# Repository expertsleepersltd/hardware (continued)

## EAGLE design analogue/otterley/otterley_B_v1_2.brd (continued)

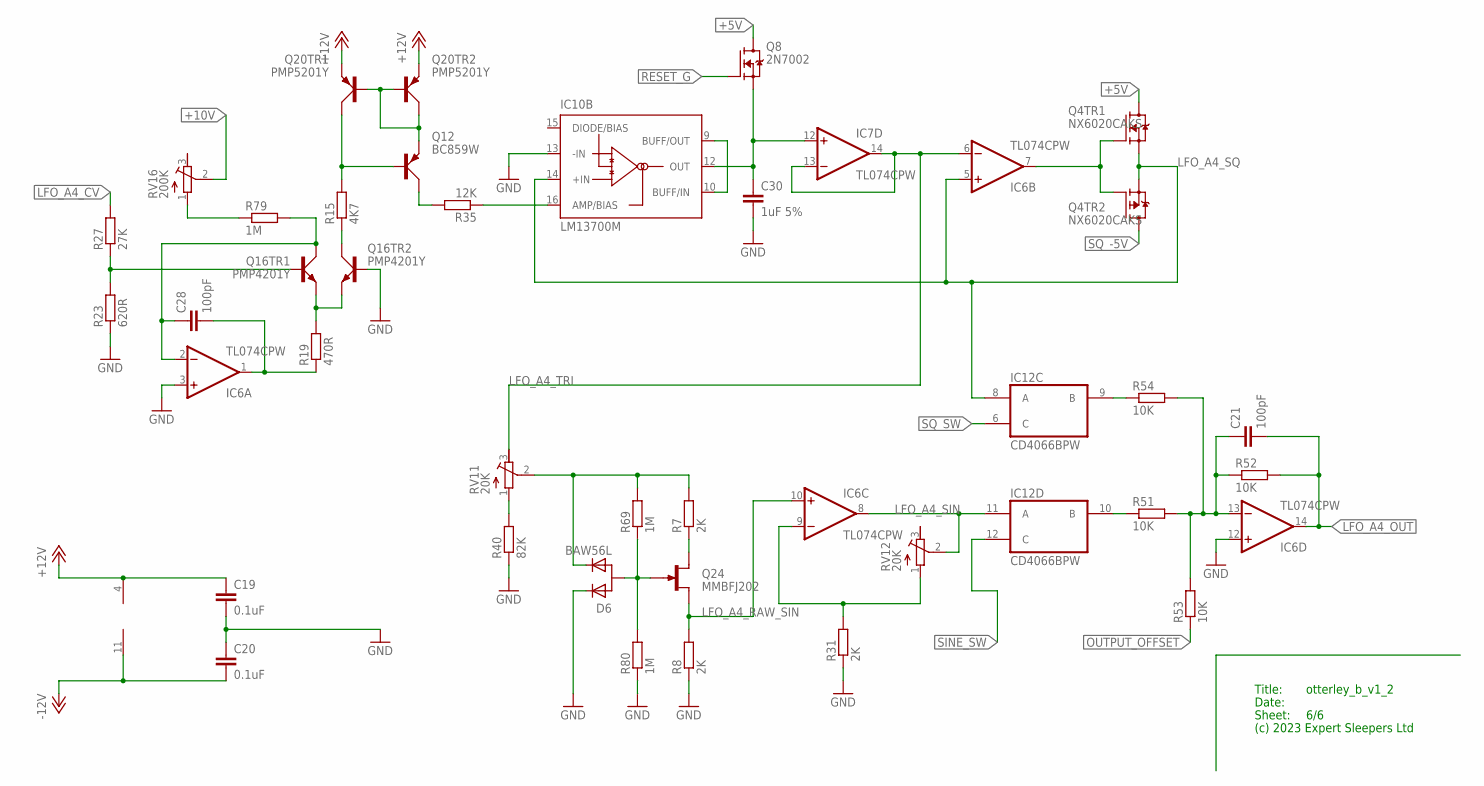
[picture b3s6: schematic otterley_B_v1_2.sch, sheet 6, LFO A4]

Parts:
C19, C20: 0.1uF; C0402
C21, C28: 100pF; C0603
C30: 1uF 5%; C0805
D6: BAW56L; SOT-23
IC6, IC7: TL074CPW; PW_R-PDSO-G14
IC10: LM13700M; SO16
IC12: CD4066BPW; PW_R-PDSO-G14
Q4: NX6020CAKS; SOT363
Q8: 2N7002; SOT23
Q12: BC859W; SOT323
Q16: PMP4201Y; SOT65P210X110-6N
Q20: PMP5201Y; SOT65P210X110-6N
Q24: MMBFJ202; SOT23
R7, R8, R31: 2K; R0603
R15: 4K7; R0603
R19: 470R; R0603
R23: 620R; R0603
R27: 27K; R0603
R35: 12K; R0603
R40: 82K; R0603
R51, R52, R53, R54: 10K; R0603
R69, R79, R80: 1M; R0603
RV11, RV12: 20K; TC33X
RV16: 200K; TC33X

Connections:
+5V: Q4.6 (D), Q8.3 (D); also elsewhere on the board
+10V: RV16.2 (S); also elsewhere on the board
+12V: C19.1, IC6.4 (V+), Q20.4 (E), Q20.5 (E); also elsewhere on the board
-12V: C20.2, IC6.11 (V-); also elsewhere on the board
GND: C19.2, C20.1, C30.2, D6.1 (C1), IC6.3 (+IN), IC6.12 (+IN), IC10.13 (-IN), Q16.2 (B), R8.1, R23.1, R31.1, R40.1, R80.1; also elsewhere on the board
LFO_A4_CV: R27.2; also elsewhere on the board
LFO_A4_OUT: C21.2, IC6.14 (OUT), R52.2; also elsewhere on the board
LFO_A4_RAW_SIN: IC6.10 (+IN), Q24.2 (S), R8.2
LFO_A4_SIN: IC6.8 (OUT), IC12.11 (A), RV12.2 (S)
LFO_A4_SQ: IC6.5 (+IN), IC10.14 (+IN), IC12.8 (A), Q4.1 (S), Q4.4 (S)
LFO_A4_TRI: IC6.6 (-IN), IC7.13 (-IN), IC7.14 (OUT), RV11.3 (E)
unnamed: IC12.9 (B), R54.1
unnamed: IC10.9 (BUFF/OUT), IC10.10 (BUFF/IN)
unnamed: C30.1, IC7.12 (+IN), IC10.12 (OUT), Q8.2 (S)
unnamed: IC10.16 (AMP/BIAS), R35.1
unnamed: C28.1, IC6.2 (-IN), Q16.6 (C), R79.2
unnamed: C28.2, IC6.1 (OUT), R19.1
unnamed: Q16.4 (E), Q16.5 (E), R19.2
unnamed: Q12.3 (C), R35.2
unnamed: Q12.1 (B), Q20.6 (C), R15.2
unnamed: Q12.2 (E), Q20.1 (B), Q20.2 (B), Q20.3 (C)
unnamed: Q16.3 (C), R15.1
unnamed: R40.2, RV11.1 (A)
unnamed: D6.2 (C2), R7.2, R69.2, RV11.2 (S)
unnamed: D6.3 (A), Q24.3 (G), R69.1, R80.2
unnamed: Q24.1 (D), R7.1
unnamed: IC6.9 (-IN), R31.2, RV12.1 (A)
unnamed: C21.1, IC6.13 (-IN), R51.2, R52.1, R53.2, R54.2
unnamed: IC6.7 (OUT), Q4.2 (G), Q4.5 (G)
unnamed: IC12.10 (B), R51.1
unnamed: R79.1, RV16.1 (A)
unnamed: Q16.1 (B), R23.2, R27.1
OUTPUT_OFFSET: R53.1; also elsewhere on the board
RESET_G: Q8.1 (G); also elsewhere on the board
SINE_SW: IC12.12 (C); also elsewhere on the board
SQ_-5V: Q4.3 (D); also elsewhere on the board
SQ_SW: IC12.6 (C); also elsewhere on the board

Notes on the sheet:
Title:
Date:
Sheet:
(c) 2023 Expert Sleepers Ltd

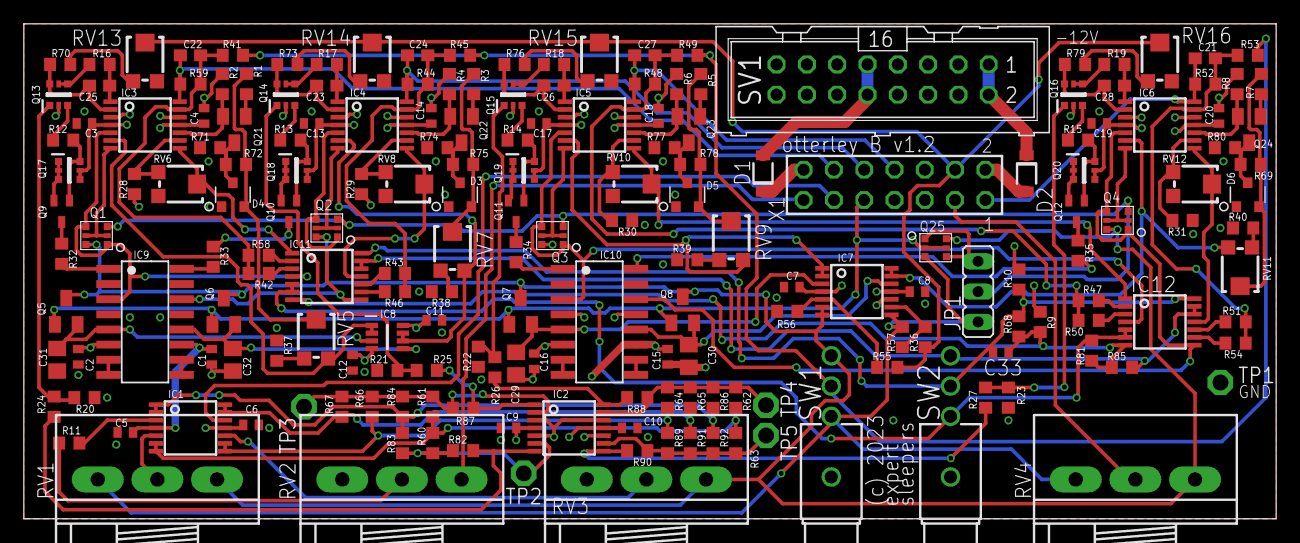
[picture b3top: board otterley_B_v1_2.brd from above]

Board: 4 copper layers, 105.0 x 41.5 mm, 194 parts (0 on the bottom side), 141 nets.

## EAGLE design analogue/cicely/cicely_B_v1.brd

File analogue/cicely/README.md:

Cicely
======

https://expert-sleepers.co.uk/cicely.html

Copyright (c) 2023 Expert Sleepers Ltd

Please refer to [LICENSE.md](LICENSE.md) for licensing information.

Please note that Expert Sleepers® is a registered trade mark in the UK, the European Union, and the United States. Remove any branding before making a derivative work.

Front panel layout is [here](../../panels).

Board and schematic are in [EAGLE](https://en.wikipedia.org/wiki/EAGLE_(program)) format.

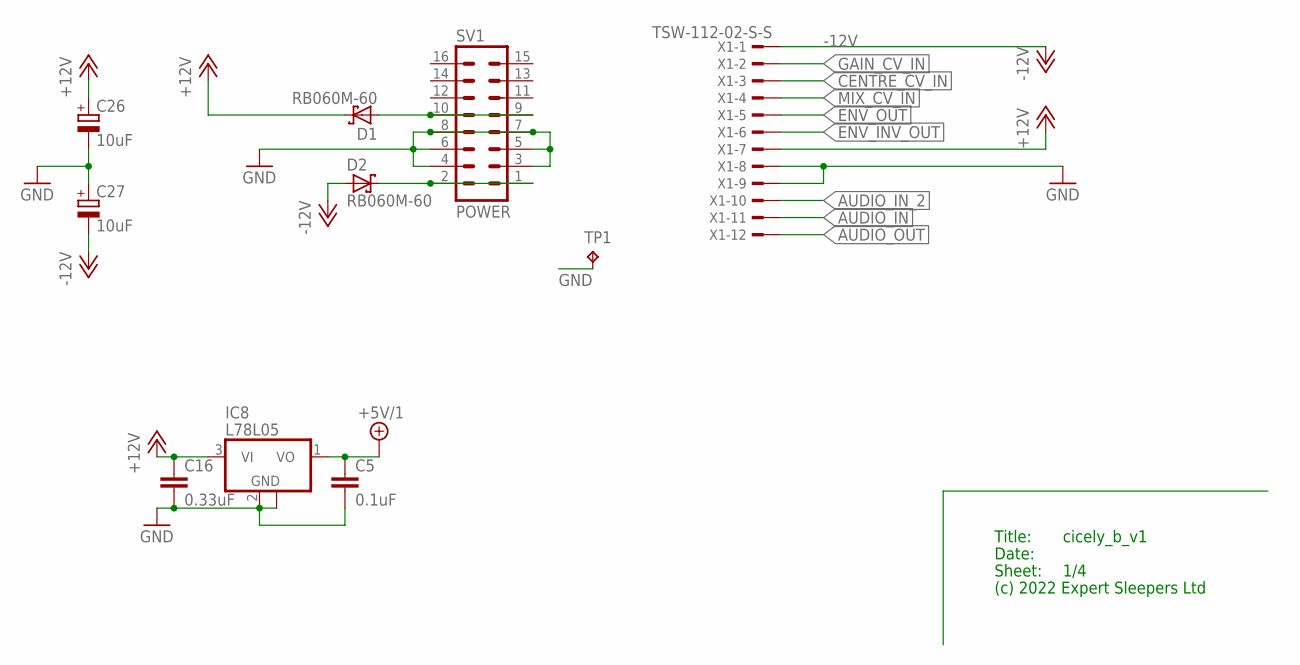
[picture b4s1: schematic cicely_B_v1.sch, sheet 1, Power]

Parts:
C5: 0.1uF; C0402
C16: 0.33uF; C0805
C26, C27: 10uF; UD-4X5,8_NICHICON
D1, D2: RB060M-60; SOD123FL
IC8: L78L05; SOT89
SV1: POWER; ML16
TP1: RA2; P1-13
X1: TSW-112-02-S-S

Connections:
+5V/1: C5.1, IC8.1 (VO); also elsewhere on the board
+12V: C16.1, C26.+, D1.C, IC8.3 (VI), X1.7; also elsewhere on the board
-12V: C27.-, D2.A, X1.1; also elsewhere on the board
AUDIO_IN: X1.11; also elsewhere on the board
AUDIO_IN_2: X1.10; also elsewhere on the board
AUDIO_OUT: X1.12; also elsewhere on the board
CENTRE_CV_IN: X1.3; also elsewhere on the board
ENV_INV_OUT: X1.6; also elsewhere on the board
ENV_OUT: X1.5; also elsewhere on the board
GAIN_CV_IN: X1.2; also elsewhere on the board
GND: C5.2, C16.2, C26.-, C27.+, IC8.2 (GND), IC8.2@1 (GND), SV1.3, SV1.4, SV1.5, SV1.6, SV1.7, SV1.8, TP1.TP, X1.8, X1.9; also elsewhere on the board
MIX_CV_IN: X1.4; also elsewhere on the board
unnamed: D2.C, SV1.1, SV1.2
unnamed: D1.A, SV1.9, SV1.10

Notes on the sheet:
Title:
Date:
Sheet:
(c) 2022 Expert Sleepers Ltd

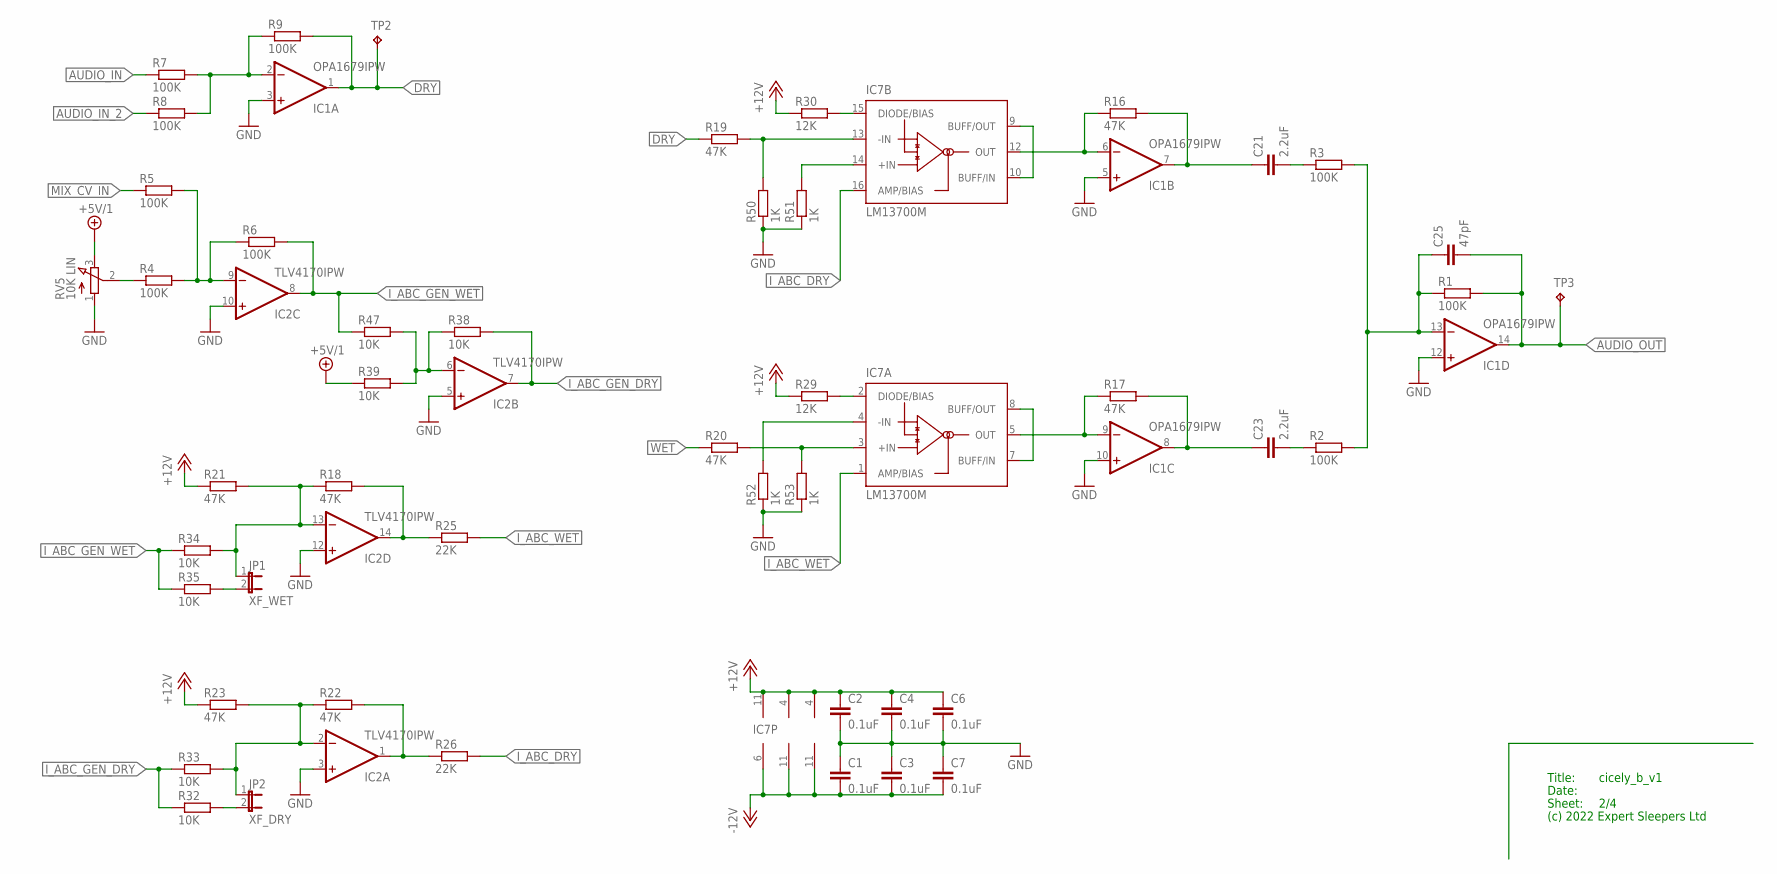
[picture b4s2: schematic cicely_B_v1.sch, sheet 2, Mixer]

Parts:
C1, C2, C3, C4, C6, C7: 0.1uF; C0402
C21, C23: 2.2uF; C0805
C25: 47pF; C0603
IC1: OPA1679IPW; PW_R-PDSO-G14
IC2: TLV4170IPW; PW_R-PDSO-G14
IC7: LM13700M; SO16
JP1: XF_WET; JP1
JP2: XF_DRY; JP1
R1, R2, R3, R4, R5, R6, R7, R8, R9: 100K; R0603
R16, R17, R18, R19, R20, R21, R22, R23: 47K; R0603
R25, R26: 22K; R0603
R29, R30: 12K; R0603
R32, R33, R34, R35, R38, R39, R47: 10K; R0603
R50, R51, R52, R53: 1K; R0603
RV5: 10K LIN; RD1610NOA0X
TP2, TP3: RA2; P1-13

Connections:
+5V/1: R39.1, RV5.3 (E); also elsewhere on the board
+12V: C2.1, C4.1, C6.1, IC1.4 (V+), IC2.4 (V+), IC7.11 (V+), R21.1, R23.1, R29.1, R30.1; also elsewhere on the board
-12V: C1.2, C3.2, C7.2, IC1.11 (V-), IC2.11 (V-), IC7.6 (V-); also elsewhere on the board
AUDIO_IN: R7.1; also elsewhere on the board
AUDIO_IN_2: R8.1; also elsewhere on the board
AUDIO_OUT: C25.2, IC1.14 (OUT), R1.2, TP3.TP; also elsewhere on the board
DRY: IC1.1 (OUT), R9.2, R19.1, TP2.TP; also elsewhere on the board
GND: C1.1, C2.2, C3.1, C4.2, C6.2, C7.1, IC1.3 (+IN), IC1.5 (+IN), IC1.10 (+IN), IC1.12 (+IN), IC2.3 (+IN), IC2.5 (+IN), IC2.10 (+IN), IC2.12 (+IN), R50.1, R51.1, R52.1, R53.1, RV5.1 (A); also elsewhere on the board
I_ABC_DRY: IC7.16 (AMP/BIAS), R26.2
I_ABC_GEN_DRY: IC2.7 (OUT), R32.1, R33.1, R38.2
I_ABC_GEN_WET: IC2.8 (OUT), R6.2, R34.1, R35.1, R47.1
I_ABC_WET: IC7.1 (AMP/BIAS), R25.2
MIX_CV_IN: R5.1; also elsewhere on the board
unnamed: C25.1, IC1.13 (-IN), R1.1, R2.2, R3.2
unnamed: R4.1, RV5.2 (S)
unnamed: IC7.15 (DIODE/BIAS), R30.2
unnamed: IC1.9 (-IN), IC7.5 (OUT), R17.1
unnamed: IC7.2 (DIODE/BIAS), R29.2
unnamed: IC1.6 (-IN), IC7.12 (OUT), R16.1
unnamed: C23.1, IC1.8 (OUT), R17.2
unnamed: IC2.9 (-IN), R4.2, R5.2, R6.1
unnamed: C21.1, IC1.7 (OUT), R16.2
unnamed: IC7.3 (+IN), R20.2, R53.2
unnamed: IC7.4 (-IN), R52.2
unnamed: IC2.13 (-IN), JP1.1, R18.1, R21.2, R34.2
unnamed: IC2.6 (-IN), R38.1, R39.2, R47.2
unnamed: IC2.14 (OUT), R18.2, R25.1
unnamed: IC2.1 (OUT), R22.2, R26.1
unnamed: IC2.2 (-IN), JP2.1, R22.1, R23.2, R33.2
unnamed: IC7.14 (+IN), R51.2
unnamed: IC7.13 (-IN), R19.2, R50.2
unnamed: C21.2, R3.1
unnamed: C23.2, R2.1
unnamed: IC7.9 (BUFF/OUT), IC7.10 (BUFF/IN)
unnamed: IC7.7 (BUFF/IN), IC7.8 (BUFF/OUT)
unnamed: IC1.2 (-IN), R7.2, R8.2, R9.1
unnamed: JP2.2, R32.2
unnamed: JP1.2, R35.2
WET: R20.1; also elsewhere on the board

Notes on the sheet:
Title:
Date:
Sheet:
(c) 2022 Expert Sleepers Ltd

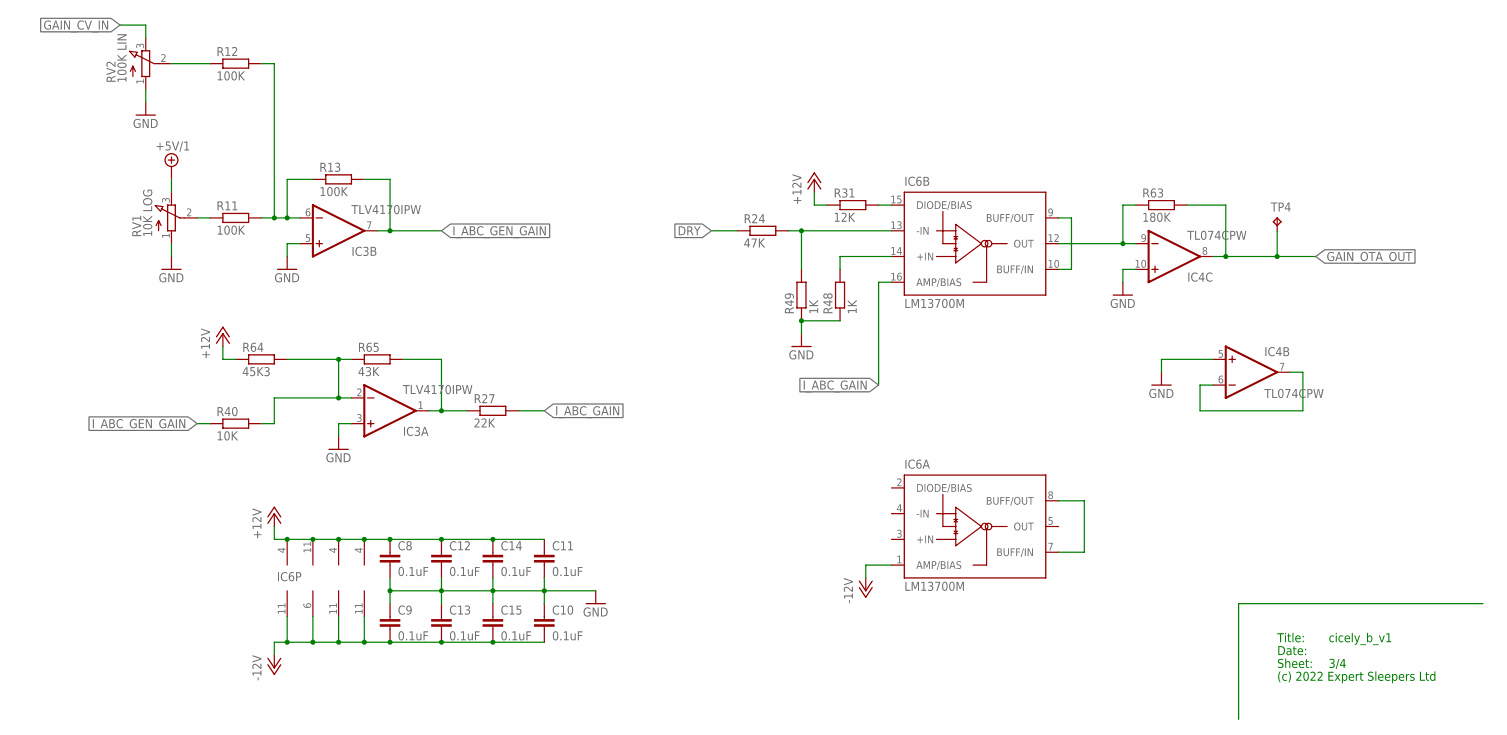
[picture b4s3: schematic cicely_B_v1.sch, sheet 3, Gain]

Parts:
C8, C9, C10, C11, C12, C13, C14, C15: 0.1uF; C0402
IC3: TLV4170IPW; PW_R-PDSO-G14
IC4, IC5: TL074CPW; PW_R-PDSO-G14
IC6: LM13700M; SO16
R11, R12, R13: 100K; R0603
R24: 47K; R0603
R27: 22K; R0603
R31: 12K; R0603
R40: 10K; R0603
R48, R49: 1K; R0603
R63: 180K; R0603
R64: 45K3; R0603
R65: 43K; R0603
RV1: 10K LOG; RD1610NOA0X
RV2: 100K LIN; RD1610NOA0X
TP4: RA2; P1-13

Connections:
+5V/1: RV1.3 (E); also elsewhere on the board
+12V: C8.1, C11.1, C12.1, C14.1, IC3.4 (V+), IC4.4 (V+), IC5.4 (V+), IC6.11 (V+), R31.1, R64.1; also elsewhere on the board
-12V: C9.2, C10.2, C13.2, C15.2, IC3.11 (V-), IC4.11 (V-), IC5.11 (V-), IC6.1 (AMP/BIAS), IC6.6 (V-); also elsewhere on the board
DRY: R24.1; also elsewhere on the board
GAIN_CV_IN: RV2.3 (E); also elsewhere on the board
GAIN_OTA_OUT: IC4.8 (OUT), R63.2, TP4.TP; also elsewhere on the board
GND: C8.2, C9.1, C10.1, C11.2, C12.2, C13.1, C14.2, C15.1, IC3.3 (+IN), IC3.5 (+IN), IC4.5 (+IN), IC4.10 (+IN), R48.1, R49.1, RV1.1 (A), RV2.1 (A); also elsewhere on the board
I_ABC_GAIN: IC6.16 (AMP/BIAS), R27.2
I_ABC_GEN_GAIN: IC3.7 (OUT), R13.2, R40.1
unnamed: IC6.9 (BUFF/OUT), IC6.10 (BUFF/IN)
unnamed: IC6.7 (BUFF/IN), IC6.8 (BUFF/OUT)
unnamed: IC6.15 (DIODE/BIAS), R31.2
unnamed: IC4.9 (-IN), IC6.12 (OUT), R63.1
unnamed: IC4.6 (-IN), IC4.7 (OUT)
unnamed: IC6.14 (+IN), R48.2
unnamed: IC6.13 (-IN), R24.2, R49.2
unnamed: R11.1, RV1.2 (S)
unnamed: IC3.6 (-IN), R11.2, R12.2, R13.1
unnamed: IC3.2 (-IN), R40.2, R64.2, R65.1
unnamed: IC3.1 (OUT), R27.1, R65.2
unnamed: R12.1, RV2.2 (S)

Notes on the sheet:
Title:
Date:
Sheet:
(c) 2022 Expert Sleepers Ltd

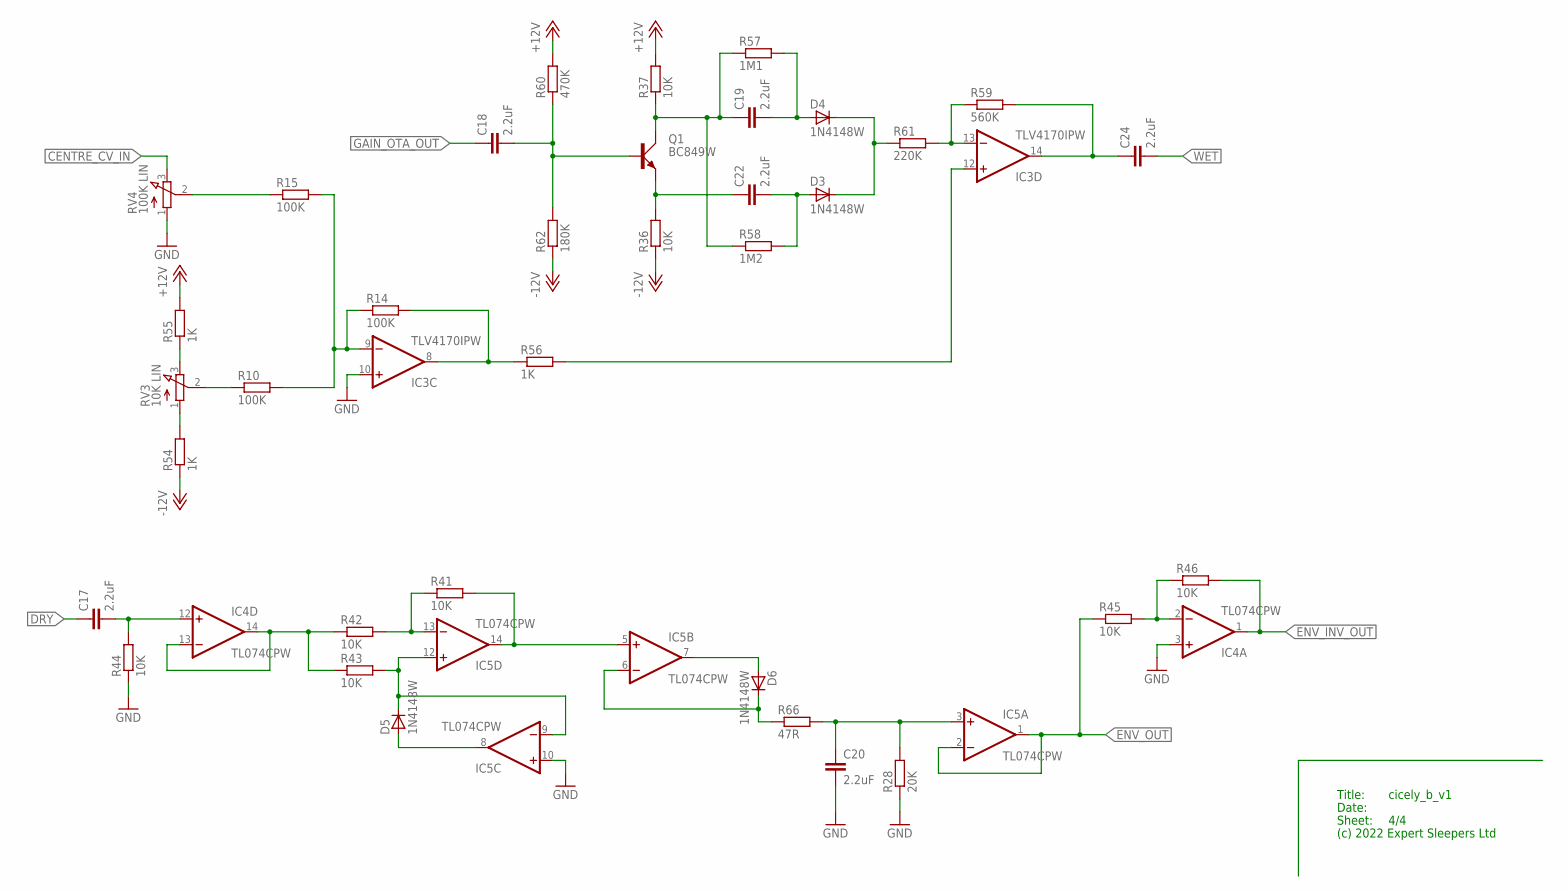
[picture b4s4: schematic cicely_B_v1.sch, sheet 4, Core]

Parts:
C17, C18, C19, C20, C22, C24: 2.2uF; C0805
D3, D4, D5, D6: 1N4148W; SOD123
IC3: TLV4170IPW; PW_R-PDSO-G14
IC4, IC5: TL074CPW; PW_R-PDSO-G14
Q1: BC849W; SOT323
R10, R14, R15: 100K; R0603
R28: 20K; R0603
R36, R37, R41, R42, R43, R44, R45, R46: 10K; R0603
R54, R55, R56: 1K; R0603
R57: 1M1; R0603
R58: 1M2; R0603
R59: 560K; R0603
R60: 470K; R0603
R61: 220K; R0603
R62: 180K; R0603
R66: 47R; R0603
RV3: 10K LIN; RD1610NOA0X
RV4: 100K LIN; RD1610NOA0X

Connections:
+12V: R37.2, R55.2, R60.2; also elsewhere on the board
-12V: R36.1, R54.1, R62.1; also elsewhere on the board
CENTRE_CV_IN: RV4.3 (E); also elsewhere on the board
DRY: C17.1; also elsewhere on the board
DRY_AC: IC4.13 (-IN), IC4.14 (OUT), R42.1, R43.1
ENV_INV_OUT: IC4.1 (OUT), R46.2; also elsewhere on the board
ENV_OUT: IC5.1 (OUT), IC5.2 (-IN), R45.1; also elsewhere on the board
GAIN_OTA_OUT: C18.1; also elsewhere on the board
GND: C20.2, IC3.10 (+IN), IC4.3 (+IN), IC5.10 (+IN), R28.1, R44.1, RV4.1 (A); also elsewhere on the board
unnamed: C17.2, IC4.12 (+IN), R44.2
unnamed: R54.2, RV3.1 (A)
unnamed: R55.1, RV3.3 (E)
unnamed: IC3.12 (+IN), R56.2
unnamed: IC3.13 (-IN), R59.1, R61.2
unnamed: C24.1, IC3.14 (OUT), R59.2
unnamed: R10.1, RV3.2 (S)
unnamed: IC3.9 (-IN), R10.2, R14.1, R15.2
unnamed: C18.2, Q1.1 (B), R60.1, R62.2
unnamed: C19.2, D4.A, R57.2
unnamed: C22.2, D3.A, R58.2
unnamed: C19.1, Q1.3 (C), R37.1, R57.1, R58.1
unnamed: C22.1, Q1.2 (E), R36.2
unnamed: D3.C, D4.C, R61.1
unnamed: IC5.13 (-IN), R41.1, R42.2
unnamed: D6.C, IC5.6 (-IN), R66.1
unnamed: IC5.5 (+IN), IC5.14 (OUT), R41.2
unnamed: D5.C, IC5.9 (-IN), IC5.12 (+IN), R43.2
unnamed: D5.A, IC5.8 (OUT)
unnamed: C20.1, IC5.3 (+IN), R28.2, R66.2
unnamed: D6.A, IC5.7 (OUT)
unnamed: IC4.2 (-IN), R45.2, R46.1
unnamed: R15.1, RV4.2 (S)
VAC_B_CV: IC3.8 (OUT), R14.2, R56.1
WET: C24.2; also elsewhere on the board

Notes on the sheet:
Title:
Date:
Sheet:
(c) 2022 Expert Sleepers Ltd

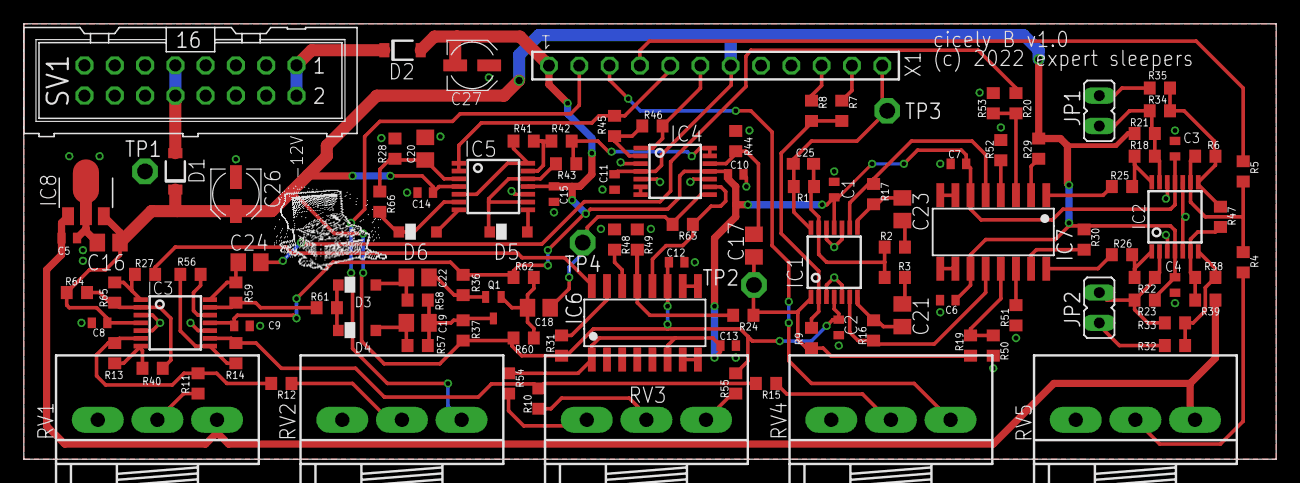
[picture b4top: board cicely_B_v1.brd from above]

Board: 2 copper layers, 105.0 x 36.5 mm, 122 parts (0 on the bottom side), 85 nets.

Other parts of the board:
U$2: TREASURE_10MM_300DPI

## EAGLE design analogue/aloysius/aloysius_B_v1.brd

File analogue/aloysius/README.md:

Aloysius
========

https://expert-sleepers.co.uk/aloysius.html

Copyright (c) 2023 Expert Sleepers Ltd

Please refer to [LICENSE.md](LICENSE.md) for licensing information.

Please note that Expert Sleepers® is a registered trade mark in the UK, the European Union, and the United States. Remove any branding before making a derivative work.

Front panel layout is [here](../../panels).

Board and schematic are in [EAGLE](https://en.wikipedia.org/wiki/EAGLE_(program)) format.

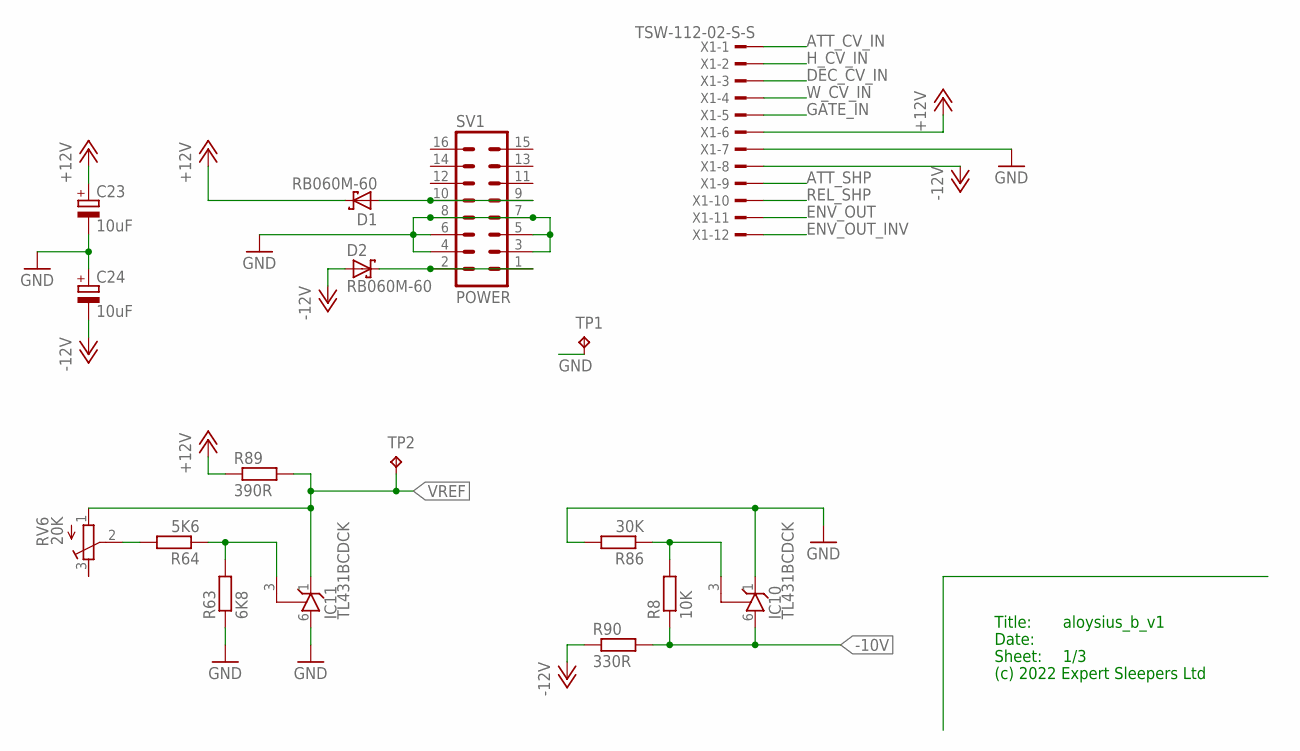
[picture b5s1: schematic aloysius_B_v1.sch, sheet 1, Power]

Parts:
C23, C24: 10uF; UD-4X5,8_NICHICON
D1, D2: RB060M-60; SOD123FL
IC10, IC11: TL431BCDCK; DCK_SC-70
R8: 10K; R0603
R63: 6K8; R0603
R64: 5K6; R0603
R86: 30K; R0603
R89: 390R; R1206
R90: 330R; R1206
RV6: 20K; TC33X
SV1: POWER; ML16
TP1, TP2: RA2; P1-13
X1: TSW-112-02-S-S

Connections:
+12V: C23.+, D1.C, R89.1, X1.6; also elsewhere on the board
-10V: IC10.6 (A), R8.1, R90.2; also elsewhere on the board
-12V: C24.-, D2.A, R90.1, X1.8; also elsewhere on the board
ATT_CV_IN: X1.1; also elsewhere on the board
ATT_SHP: X1.9; also elsewhere on the board
DEC_CV_IN: X1.3; also elsewhere on the board
ENV_OUT: X1.11; also elsewhere on the board
ENV_OUT_INV: X1.12; also elsewhere on the board
GATE_IN: X1.5; also elsewhere on the board
GND: C23.-, C24.+, IC10.1 (C), IC11.6 (A), R63.1, R86.2, SV1.3, SV1.4, SV1.5, SV1.6, SV1.7, SV1.8, TP1.TP, X1.7; also elsewhere on the board
H_CV_IN: X1.2; also elsewhere on the board
unnamed: D2.C, SV1.1, SV1.2
unnamed: D1.A, SV1.9, SV1.10
unnamed: IC11.3 (R), R63.2, R64.1
unnamed: R64.2, RV6.2 (S)
unnamed: IC10.3 (R), R8.2, R86.1
REL_SHP: X1.10; also elsewhere on the board
VREF: IC11.1 (C), R89.2, RV6.1 (A), TP2.TP; also elsewhere on the board
W_CV_IN: X1.4; also elsewhere on the board

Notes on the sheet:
Title:
Date:
Sheet:
(c) 2022 Expert Sleepers Ltd

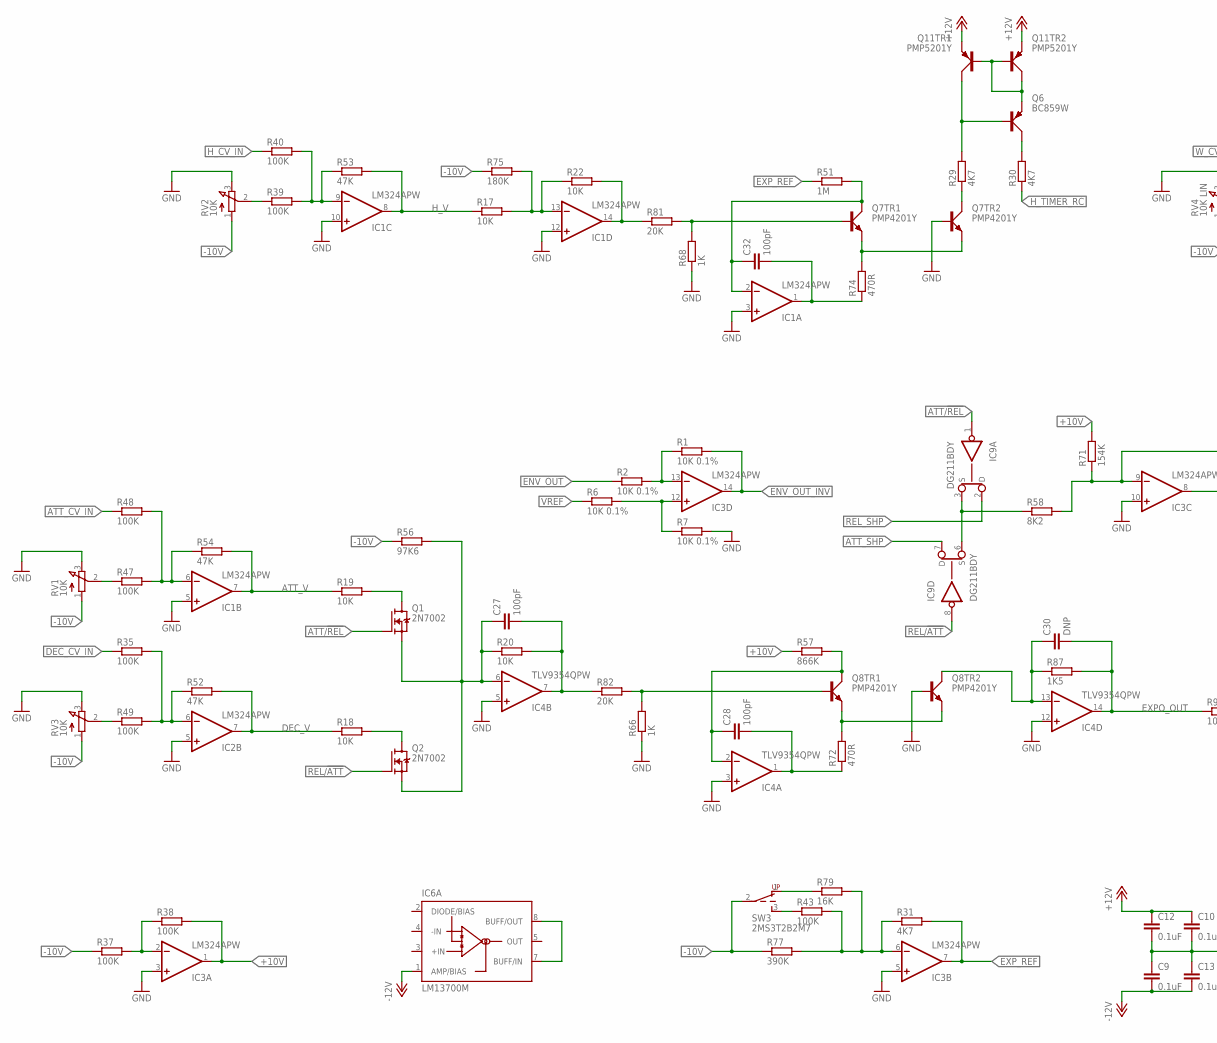
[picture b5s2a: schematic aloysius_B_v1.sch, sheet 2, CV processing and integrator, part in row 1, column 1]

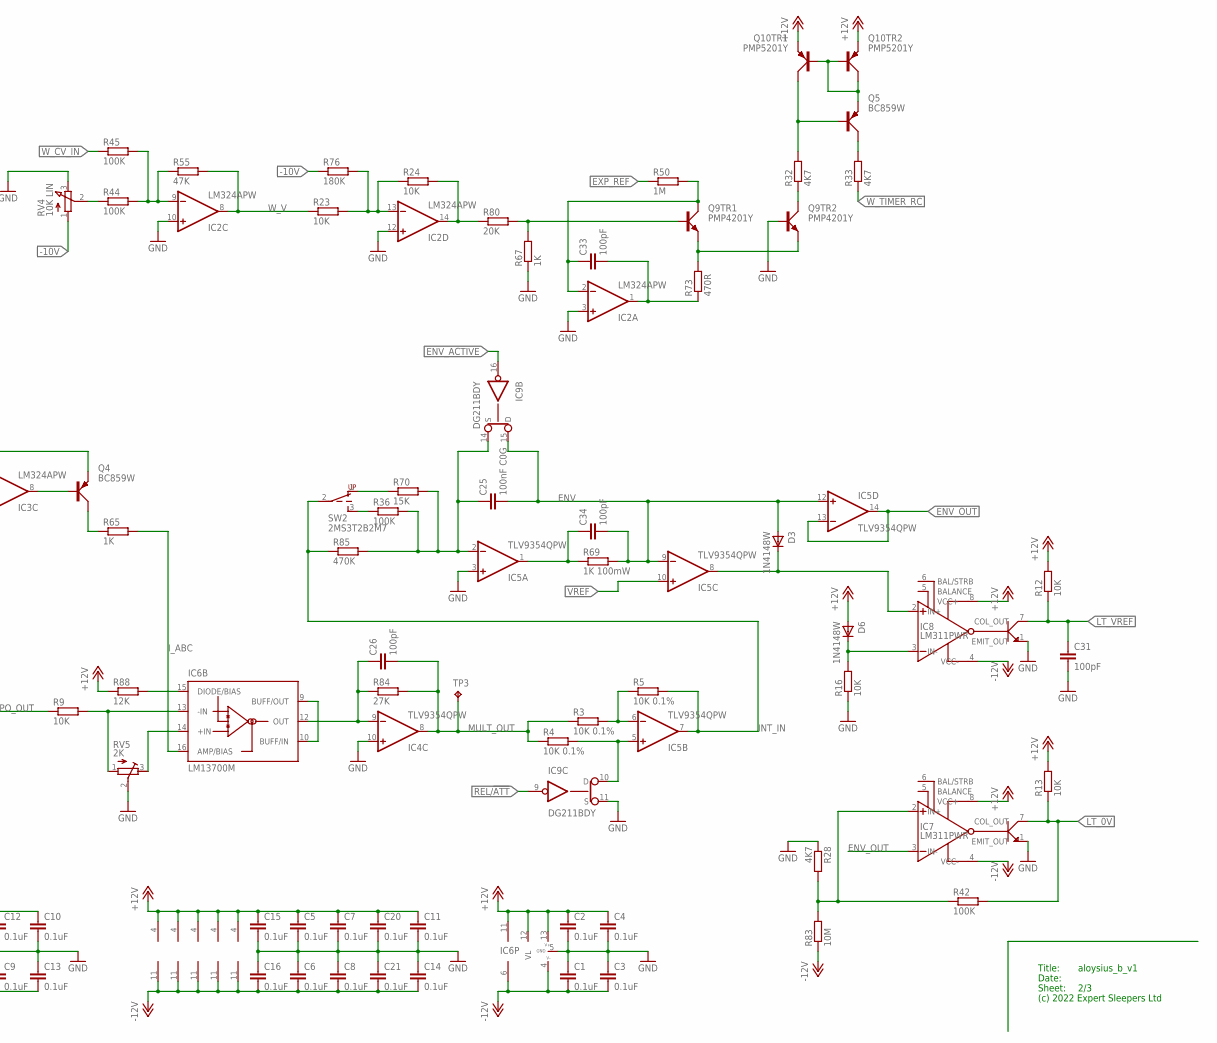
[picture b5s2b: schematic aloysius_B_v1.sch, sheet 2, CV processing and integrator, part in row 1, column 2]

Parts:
C1, C2, C3, C4, C5, C6, C7, C8, C9, C10, C11, C12, C13, C14, C15, C16, C20, C21: 0.1uF; C0402
C25: 100nF C0G; C1206
C26, C27, C28, C31, C32, C33, C34: 100pF; C0603
C30: DNP; C0603
D3, D6: 1N4148W; SOD123
IC1, IC2, IC3: LM324APW; PW_R-PDSO-G14
IC4, IC5: TLV9354QPW; PW_R-PDSO-G14
IC6: LM13700M; SO16
IC7, IC8: LM311PWR; SOP65P640X120-8N
IC9: DG211BDY; SO16
Q1, Q2: 2N7002; SOT23
Q4, Q5, Q6: BC859W; SOT323
Q7, Q8, Q9: PMP4201Y; SOT65P210X110-6N
Q10, Q11: PMP5201Y; SOT65P210X110-6N
R1, R2, R3, R4, R5, R6, R7: 10K 0.1%; R0603
R9, R12, R13, R16, R17, R18, R19, R20, R22, R23, R24: 10K; R0603
R28, R29, R30, R31, R32, R33: 4K7; R0603
R35, R36, R37, R38, R39, R40, R42, R43, R44, R45, R47, R48, R49: 100K; R0603
R50, R51: 1M; R0603
R52, R53, R54, R55: 47K; R0603
R56: 97K6; R0603
R57: 866K; R0603
R58: 8K2; R0603
R65, R66, R67, R68: 1K; R0603
R69: 1K 100mW; R0603
R70: 15K; R0603
R71: 154K; R0603
R72, R73, R74: 470R; R0603
R75, R76: 180K; R0603
R77: 390K; R0603
R79: 16K; R0603
R80, R81, R82: 20K; R0603
R83: 10M; R0603
R84: 27K; R0603
R85: 470K; R0603
R87: 1K5; R0603
R88: 12K; R0603
RV1, RV2, RV3: 10K; RD1610NOA0X
RV4: 10K LIN; RD1610NOA0X
RV5: 2K; RTRIM3296W
SW2, SW3: 2MS3T2B2M7; 2MS1T2B2M7RE
TP3: RA2; P1-13

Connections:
+10V: IC3.1 (OUT), R38.2, R57.1, R71.2
+12V: C2.1, C4.1, C5.1, C7.1, C10.1, C11.1, C12.1, C15.1, C20.1, D6.A, IC1.4 (V+), IC2.4 (V+), IC3.4 (V+), IC4.4 (V+), IC5.4 (V+), IC6.11 (V+), IC7.8 (VCC+), IC8.8 (VCC+), IC9.12 (VL), IC9.13 (V+), Q10.4 (E), Q10.5 (E), Q11.4 (E), Q11.5 (E), R12.2, R13.2, R88.1; also elsewhere on the board
-10V: R37.1, R56.1, R75.1, R76.1, R77.1, RV1.1 (A), RV2.1 (A), RV3.1 (A), RV4.1 (A), SW3.2 (PR); also elsewhere on the board
-12V: C1.2, C3.2, C6.2, C8.2, C9.2, C13.2, C14.2, C16.2, C21.2, IC1.11 (V-), IC2.11 (V-), IC3.11 (V-), IC4.11 (V-), IC5.11 (V-), IC6.1 (AMP/BIAS), IC6.6 (V-), IC7.4 (VCC-), IC8.4 (VCC-), IC9.4 (V-), R83.1; also elsewhere on the board
ATT/!REL: IC9.1 (IN), Q1.1 (G); also elsewhere on the board
ATT_CV_IN: R48.1; also elsewhere on the board
ATT_SHP: IC9.7 (D); also elsewhere on the board
ATT_V: IC1.7 (OUT), R19.1, R54.2
DEC_CV_IN: R35.1; also elsewhere on the board
DEC_V: IC2.7 (OUT), R18.1, R52.2
ENV: C25.2, C34.2, D3.A, IC5.9 (-IN), IC5.12 (+IN), IC9.15 (D), R69.2
ENV_ACTIVE: IC9.16 (IN); also elsewhere on the board
ENV_OUT: IC5.13 (-IN), IC5.14 (OUT), IC7.3 (IN-), R2.1; also elsewhere on the board
ENV_OUT_INV: IC3.14 (OUT), R1.2; also elsewhere on the board
EXPO_OUT: C30.2, IC4.14 (OUT), R9.1, R87.2
EXP_REF: IC3.7 (OUT), R31.2, R50.1, R51.1
GND: C1.1, C2.2, C3.1, C4.2, C5.2, C6.1, C7.2, C8.1, C9.1, C10.2, C11.2, C12.2, C13.1, C14.1, C15.2, C16.1, C20.2, C21.1, C31.2, IC1.3 (+IN), IC1.5 (+IN), IC1.10 (+IN), IC1.12 (+IN), IC2.3 (+IN), IC2.5 (+IN), IC2.10 (+IN), IC2.12 (+IN), IC3.3 (+IN), IC3.5 (+IN), IC3.10 (+IN), IC4.3 (+IN), IC4.5 (+IN), IC4.10 (+IN), IC4.12 (+IN), IC5.3 (+IN), IC7.1 (EMIT_OUT), IC8.1 (EMIT_OUT), IC9.5 (GND), IC9.11 (S), Q7.2 (B), Q8.2 (B), Q9.2 (B), R7.2, R16.1, R28.1, R66.1, R67.1, R68.1, RV1.3 (E), RV2.3 (E), RV3.3 (E), RV4.3 (E), RV5.2 (S); also elsewhere on the board
H_CV_IN: R40.1; also elsewhere on the board
H_TIMER_RC: R30.1; also elsewhere on the board
H_V: IC1.8 (OUT), R17.1, R53.2
INT_IN: IC5.7 (OUT), R5.2, R85.1, SW2.2 (PR)
I_ABC: IC6.16 (AMP/BIAS), R65.2
LT_0V: IC7.7 (COL_OUT), R13.1, R42.2; also elsewhere on the board
LT_VREF: C31.1, IC8.7 (COL_OUT), R12.1; also elsewhere on the board
MULT_OUT: C26.2, IC4.8 (OUT), R3.1, R4.1, R84.2, TP3.TP
unnamed: IC3.13 (-IN), R1.1, R2.2
unnamed: C34.1, IC5.1 (OUT), R69.1
unnamed: D3.C, IC5.8 (OUT), IC8.2 (IN+)
unnamed: C32.1, IC1.2 (-IN), Q7.6 (C), R51.2
unnamed: C30.1, IC4.13 (-IN), Q8.3 (C), R87.1
unnamed: C26.1, IC4.9 (-IN), IC6.12 (OUT), R84.1
unnamed: IC6.15 (DIODE/BIAS), R88.2
unnamed: IC5.6 (-IN), R3.2, R5.1
unnamed: IC6.13 (-IN), R9.2, RV5.1 (A)
unnamed: IC6.7 (BUFF/IN), IC6.8 (BUFF/OUT)
unnamed: C32.2, IC1.1 (OUT), R74.1
unnamed: D6.C, IC8.3 (IN-), R16.2
unnamed: Q7.4 (E), Q7.5 (E), R74.2
unnamed: IC1.14 (OUT), R22.2, R81.1
unnamed: R39.1, RV2.2 (S)
unnamed: Q7.1 (B), R68.2, R81.2
unnamed: Q6.3 (C), R30.2
unnamed: R79.1, SW3.1 (RU)
unnamed: IC1.9 (-IN), R39.2, R40.2, R53.1
unnamed: Q1.3 (D), R19.2
unnamed: C27.2, IC4.7 (OUT), R20.2, R82.1
unnamed: Q6.1 (B), Q11.6 (C), R29.2
unnamed: Q6.2 (E), Q11.1 (B), Q11.2 (B), Q11.3 (C)
unnamed: R43.1, SW3.3 (RD)
unnamed: IC3.12 (+IN), R6.2, R7.1
unnamed: Q7.3 (C), R29.1
unnamed: IC7.2 (IN+), R28.2, R42.1, R83.2
unnamed: IC3.6 (-IN), R31.1, R43.2, R77.2, R79.2
unnamed: C25.1, IC5.2 (-IN), IC9.14 (S), R36.2, R70.2, R85.2
unnamed: IC3.8 (OUT), Q4.1 (B)
unnamed: R44.1, RV4.2 (S)
unnamed: IC5.5 (+IN), IC9.10 (D), R4.2
unnamed: R47.1, RV1.2 (S)
unnamed: Q2.3 (D), R18.2
unnamed: IC2.9 (-IN), R44.2, R45.2, R55.1
unnamed: IC1.13 (-IN), R17.2, R22.1, R75.2
unnamed: C27.1, IC4.6 (-IN), Q1.2 (S), Q2.2 (S), R20.1, R56.2
unnamed: Q8.1 (B), R66.2, R82.2
unnamed: IC6.14 (+IN), RV5.3 (E)
unnamed: IC1.6 (-IN), R47.2, R48.2, R54.1
unnamed: R49.1, RV3.2 (S)
unnamed: IC2.6 (-IN), R35.2, R49.2, R52.1
unnamed: R36.1, SW2.3 (RD)
unnamed: C28.1, IC4.2 (-IN), Q8.6 (C), R57.2
unnamed: C28.2, IC4.1 (OUT), R72.1
unnamed: IC3.9 (-IN), Q4.2 (E), R58.2, R71.1
unnamed: R70.1, SW2.1 (RU)
unnamed: Q8.4 (E), Q8.5 (E), R72.2
unnamed: IC2.13 (-IN), R23.2, R24.1, R76.2
unnamed: C33.1, IC2.2 (-IN), Q9.6 (C), R50.2
unnamed: IC3.2 (-IN), R37.2, R38.1
unnamed: C33.2, IC2.1 (OUT), R73.1
unnamed: Q9.4 (E), Q9.5 (E), R73.2
unnamed: IC2.14 (OUT), R24.2, R80.1
unnamed: Q9.1 (B), R67.2, R80.2
unnamed: Q4.3 (C), R65.1
unnamed: IC9.3 (S), IC9.6 (S), R58.1
unnamed: Q5.3 (C), R33.2
unnamed: Q5.1 (B), Q10.6 (C), R32.2
unnamed: IC6.9 (BUFF/OUT), IC6.10 (BUFF/IN)
unnamed: Q5.2 (E), Q10.1 (B), Q10.2 (B), Q10.3 (C)
unnamed: Q9.3 (C), R32.1
REL/!ATT: IC9.8 (IN), IC9.9 (IN), Q2.1 (G); also elsewhere on the board
REL_SHP: IC9.2 (D); also elsewhere on the board
VREF: IC5.10 (+IN), R6.1; also elsewhere on the board
W_CV_IN: R45.1; also elsewhere on the board
W_TIMER_RC: R33.1; also elsewhere on the board
W_V: IC2.8 (OUT), R23.1, R55.2

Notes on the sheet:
Title:
Date:
Sheet:
(c) 2022 Expert Sleepers Ltd
